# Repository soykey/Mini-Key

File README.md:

# Mini-key

このプロジェクトは，自作キーボードの回路図とファームウェアとそのファームウェアで使用されるライブラリを格納しています．キーボードは3x2の6キーキーボードでマイコンはSeeed Studio XIAO RP2040を使用しています．

## 回路図

回路図はKiCadで作成しました．

## ファームウェア

ファームウェアはCircuitPythonで書きました。以下のファイルがあります．

- `code.py`: メインのプログラムです．キー入力を検出し，対応するキーコードをUSB HIDデバイスとして送信します．
- `lib/`: ファームウェアで使用されるライブラリが入っているディレクトリです．以下のライブラリが必要です．
- `adafruit_hid`: USB HIDデバイスとして動作するためのライブラリです．

## 使い方

### 組み立て

キースイッチはお好みのCherry MX互換のものを使用してください．ダイオードの指定は特にありません．XIAO RP2040と1x7ピンヘッダとダイオード，キースイッチをはんだ付けしキーキャップを取り付ければ完成です．

### ファームウェアの書き込みと更新

ファームウェアを書き込むには，まずXIAO RP2040にCircuitPythonをインストールする必要があります．[Thonny](https://thonny.org/)というエディターをダウンロードし，起動後，右下のインタプリタ設定からCircuitPython(ジェネリック)を選択し，`Install or update CircuitPython(UF2)`をクリックしてインストールするドライブ，ボードの種類，バージョンを選んでください．

CircuitPythonをインストールしたXIAO RP2040をPCに接続すると，CIRCUITPYという名前のドライブが認識されます．このドライブに`code.py`，`lib`ディレクトリをコピーしてください．

ファームウェアを更新する場合は，同じようにCIRCUITPYドライブに新しいファイルやディレクトリをコピーすれば反映されます．

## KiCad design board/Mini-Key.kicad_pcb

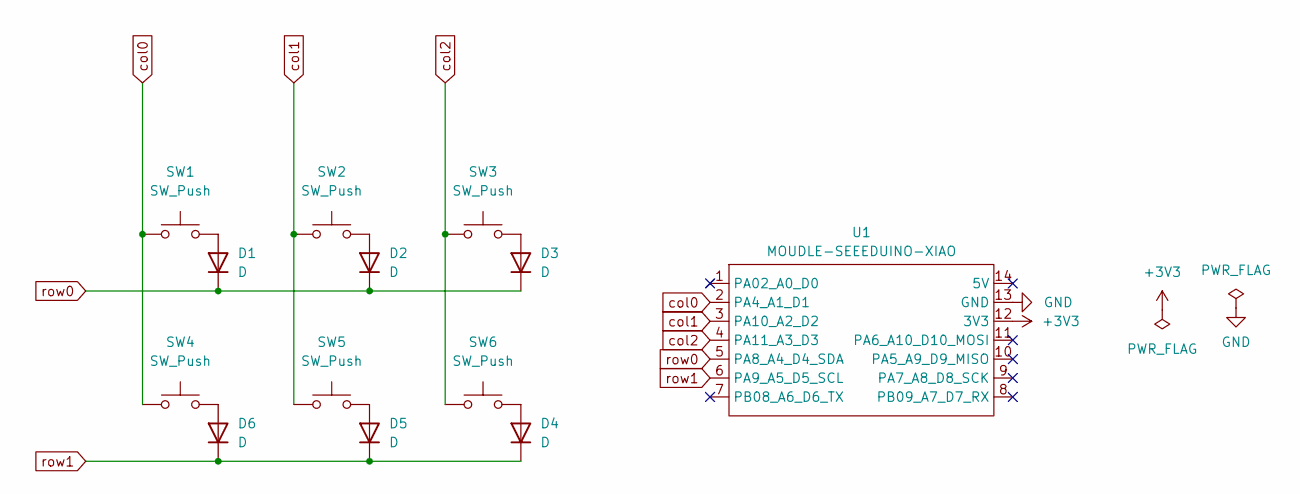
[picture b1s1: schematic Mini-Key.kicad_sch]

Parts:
D1, D2, D3, D4, D5, D6: D; Diode_TH
SW1, SW2, SW3, SW4, SW5, SW6: SW_Push; CherryMX_Solder_1u
U1: MOUDLE-SEEEDUINO-XIAO; MOUDLE14P-2.54-21X17.8MM

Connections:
+3V3: U1.12 (3V3)
GND: U1.13 (GND)
unnamed: D1.2 (A), SW1.2
unnamed: D2.2 (A), SW2.2
unnamed: D3.2 (A), SW3.2
unnamed: D4.2 (A), SW6.2
unnamed: D5.2 (A), SW5.2
unnamed: D6.2 (A), SW4.2
col0: SW1.1, SW4.1, U1.2 (PA4_A1_D1)
col1: SW2.1, SW5.1, U1.3 (PA10_A2_D2)
col2: SW3.1, SW6.1, U1.4 (PA11_A3_D3)
row0: D1.1 (K), D2.1 (K), D3.1 (K), U1.5 (PA8_A4_D4_SDA)
row1: D4.1 (K), D5.1 (K), D6.1 (K), U1.6 (PA9_A5_D5_SCL)

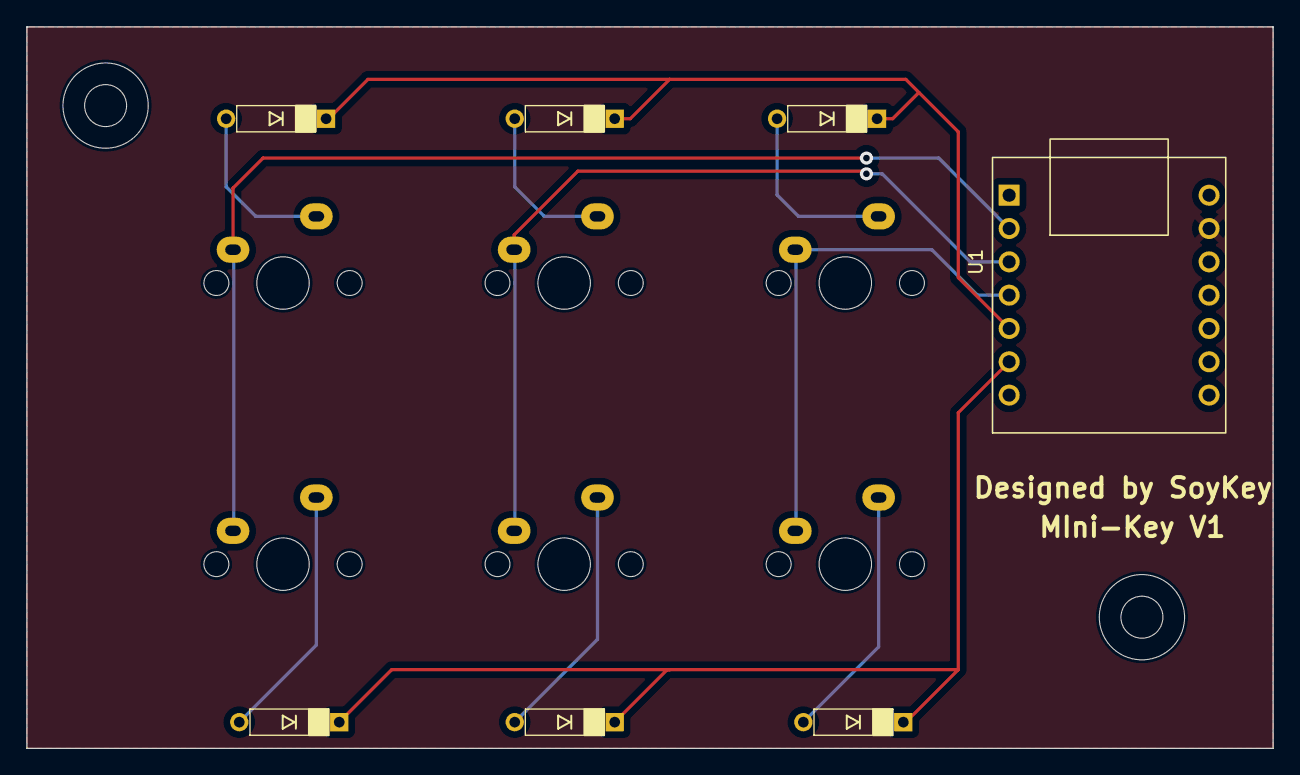
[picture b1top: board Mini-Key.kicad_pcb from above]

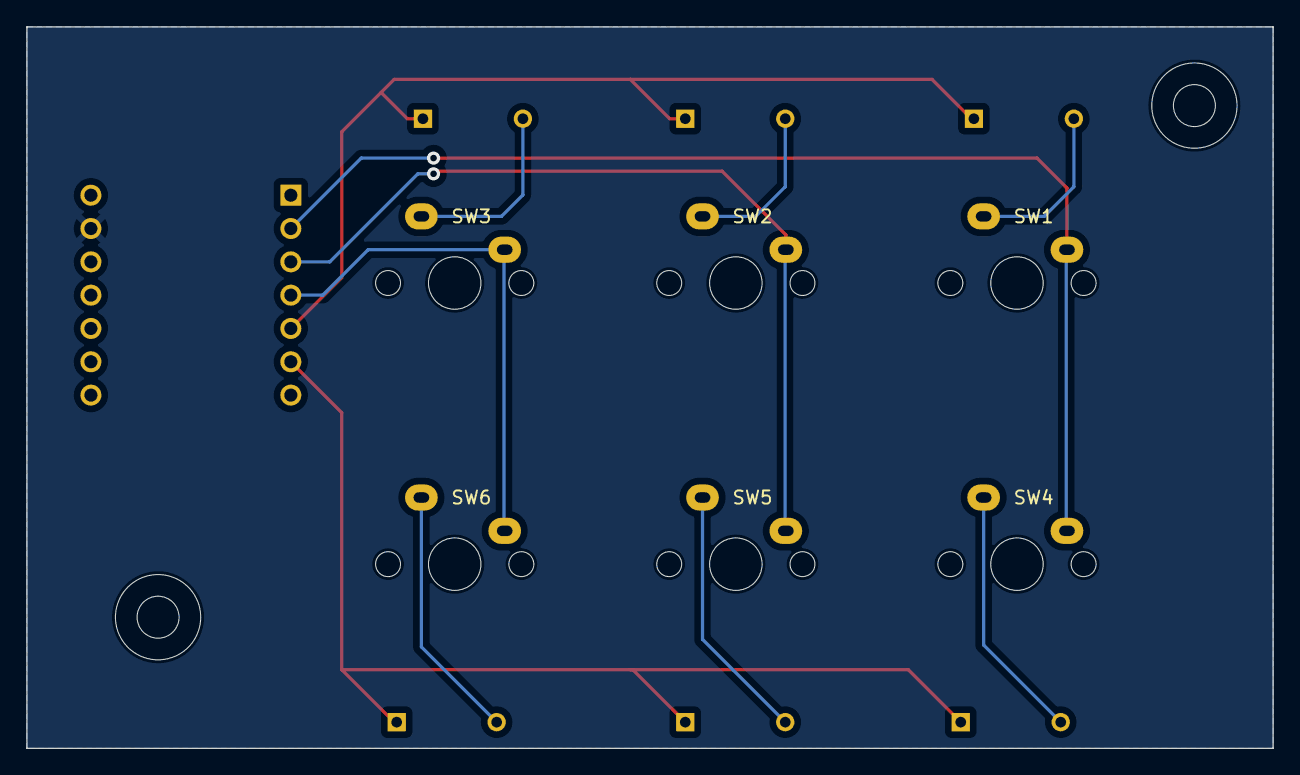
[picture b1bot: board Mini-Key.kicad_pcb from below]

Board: 2 copper layers, 95.0 x 55.0 mm, 17 parts (6 on the bottom side), 11 nets.

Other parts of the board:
Ref**: Val**; m3_Screw_Hole_EdgeCuts
Ref**#2, Ref**#4: Val**; m3_Spacer_Hole
Ref**#3: Val**; m3_Screw_Hole_EdgeCuts

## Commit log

2023-10-09 Fix place
2023-10-09 update lib
